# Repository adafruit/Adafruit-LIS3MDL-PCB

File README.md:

## Adafruit LIS3MDL Triple-axis Magnetometer PCB

<a href="http://www.adafruit.com/products/4479"><br/>
Click here to purchase one from the Adafruit shop</a>

PCB files for the Adafruit LIS3MDL Triple-axis Magnetometer. 

Format is EagleCAD schematic and board layout
* https://www.adafruit.com/product/4479

### Description

Sense the magnetic fields that surround us with this handy triple-axis magnetometer (compass) module. Magnetometers can sense where the strongest magnetic force is coming from, generally used to detect magnetic north, but can also be used for measuring magnetic fields. This sensor tends to be paired with a 6-DoF (degree of freedom) accelerometer/gyroscope to create a 9-DoF inertial measurement unit that can detect its orientation in real-space thanks to Earth's stable magnetic field. It's a great match for the LSM6DSOX from ST!

We based this breakout on ST's LIS3MDL, a great general purpose magnetometer. This compact sensor uses I2C to communicate and its very easy to use. Simply download our library and connect the SCL pin to your I2C clock pin, and SDA pin to your I2C data pin and upload our test program to read out magnetic field data. If you'd like, you can also use SPI to receive data (we just happen to prefer I2C here)

This sensor can sense ranges from +-4 gauss (+- 400 uTesla) up to +-16 gauss (+- 16uTesla). For ultra high precision, 155 Hz update rate is recommended - but if you don't mind a little loss of precision, the sensor can output at 1000 Hz.

To make life easier so you can focus on your important work, we've taken the LIS3MDL and put it onto a breakout PCB along with support circuitry to let you use this little wonder with 3.3V (Feather/Raspberry Pi) or 5V (Arduino/ Metro328) logic levels. Additionally since it speaks I2C you can easily connect it up with two wires (plus power and ground!).  We've even included SparkFun qwiic compatible STEMMA QT connectors for the I2C bus so you don't even need to solder! Just wire up to your favorite micro and you can use our CircuitPython/Python or Arduino drivers to easily interface with the LIS3MDL and get magnetic measurements ASAP.

### License

Adafruit invests time and resources providing this open source design, please support Adafruit and open-source hardware by purchasing products from [Adafruit](https://www.adafruit.com)!

Designed by Limor Fried/Ladyada for Adafruit Industries.

Creative Commons Attribution/Share-Alike, all text above must be included in any redistribution. 
See license.txt for additional details.

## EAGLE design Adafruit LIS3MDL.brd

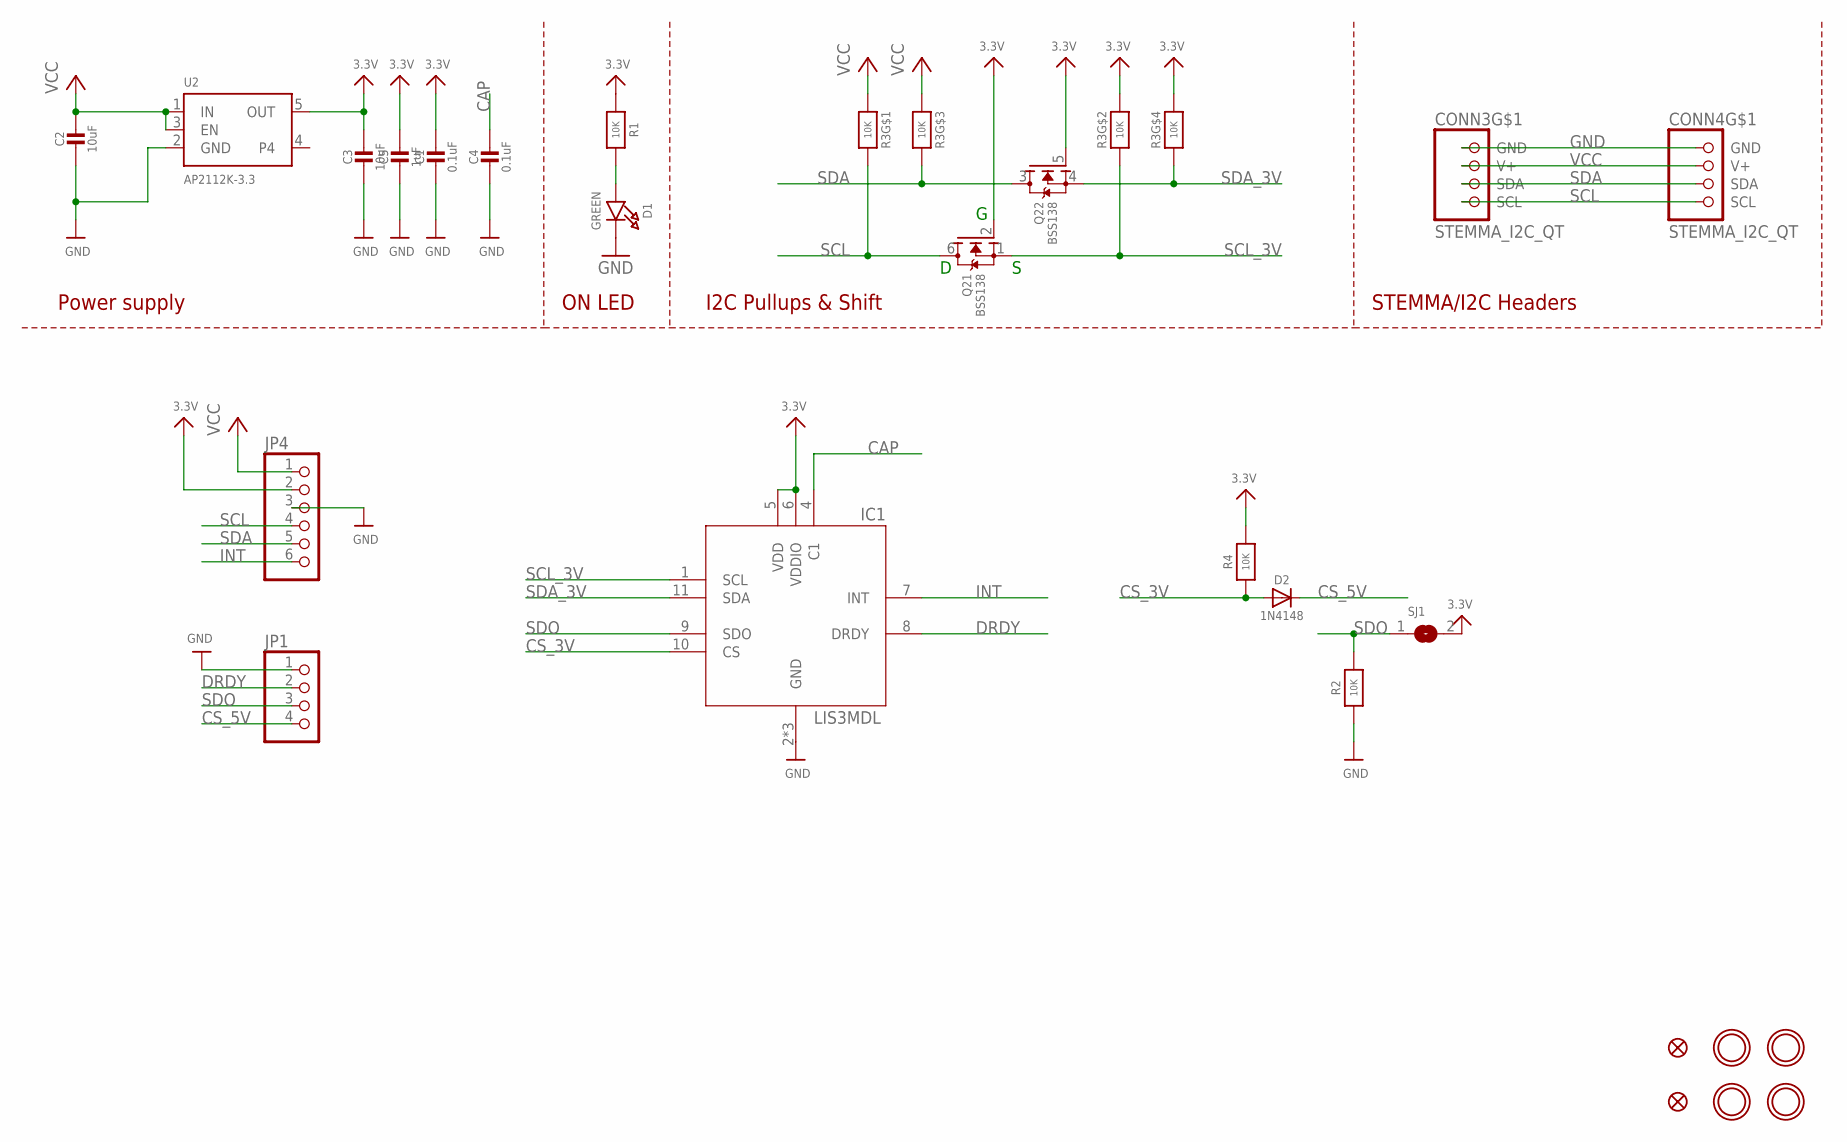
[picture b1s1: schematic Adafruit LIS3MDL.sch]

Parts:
C1, C4: 0.1uF; 0603-NO
C2, C3: 10uF; 0805-NO
C5: 1uF; 0603-NO
CONN3, CONN4: STEMMA_I2C_QT; JST_SH4
D1: GREEN; CHIPLED_0603_NOOUTLINE
D2: 1N4148; SOD-323
FID3, FID4: FIDUCIAL_1MM
IC1: LIS3MDL; LGA12_2X2MM
JP1: HEADER-1X4ROUND; 1X04_ROUND
JP4: HEADER-1X670MIL; 1X06_ROUND_70
Q2: BSS138; SOT363
R1, R2, R4: 10K; 0603-NO
R3: 10K; RESPACK_4X0603
SJ1: SOLDERJUMPER; SOLDERJUMPER_ARROW_NOPASTE
U2: AP2112K-3.3; SOT23-5
U$1, U$17, U$19, U$21: MOUNTINGHOLE2.5; MOUNTINGHOLE_2.5_PLATED

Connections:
3.3V: C1.1, C3.1, C5.1, IC1.5 (VDD), IC1.6 (VDDIO), JP4.2, Q2.2 (G), Q2.5 (G), R1.1, R3.2 (1), R3.4 (1), R4.2, SJ1.2, U2.5 (OUT)
CAP: C4.1, IC1.4 (C1)
CS_3V: D2.A, IC1.10 (CS), R4.1
CS_5V: D2.C, JP1.4
DRDY: IC1.8 (DRDY), JP1.2
GND: C1.2, C2.2, C3.2, C4.2, C5.2, CONN3.1 (GND), CONN4.1 (GND), D1.C, IC1.2 (GND), IC1.3 (GND), IC1.12 (GND), JP1.1, JP4.3, R2.1, U2.2 (GND)
INT: IC1.7 (INT), JP4.6
unnamed: D1.A, R1.2
SCL: CONN3.4 (SCL), CONN4.4 (SCL), JP4.4, Q2.6 (D), R3.8 (2)
SCL_3V: IC1.1 (SCL), Q2.1 (S), R3.7 (2)
SDA: CONN3.3 (SDA), CONN4.3 (SDA), JP4.5, Q2.3 (D), R3.6 (2)
SDA_3V: IC1.11 (SDA), Q2.4 (S), R3.5 (2)
SDO: IC1.9 (SDO), JP1.3, R2.2, SJ1.1
VCC: C2.1, CONN3.2 (V+), CONN4.2 (V+), JP4.1, R3.1, R3.3 (1), U2.1 (IN), U2.3 (EN)

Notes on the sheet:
I2C Pullups & Shift
STEMMA/I2C Headers
ON LED
Power supply

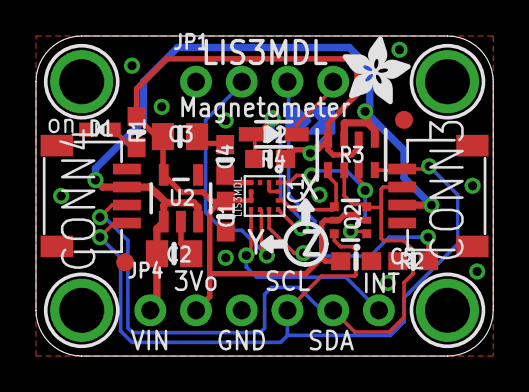
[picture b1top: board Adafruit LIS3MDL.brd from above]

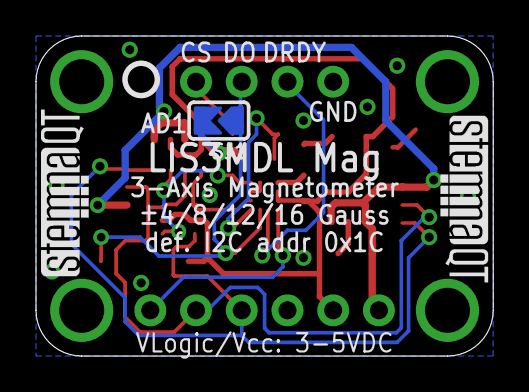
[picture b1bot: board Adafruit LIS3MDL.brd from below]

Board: 2 copper layers, 25.4 x 17.8 mm, 29 parts (4 on the bottom side), 14 nets.

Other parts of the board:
U$11: ADAFRUIT_3.5MM
U$25: PCBFEAT-REV-040
U$30, U$31: STEMMAQT

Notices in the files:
parts and their libraries:
microbuilder: This work is placed in the public domain, and may be freely used for commercial and non-commercial work with the following conditions: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
